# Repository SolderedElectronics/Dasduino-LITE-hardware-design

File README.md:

# Dasduino LITE Hardware Design

## About the Product

|  |
| :----------------------------------------------------------: |
| [Buy Dasduino LITE](https://www.solde.red/333008) |

Dasduino Lite is the right choice when you are limited with space, but still looking for capable controller. Based on Attiny1604, with USB-C port, Li-ion charger and CH340 USB-UART converter, it has all must-haves on a small form-factor.

Only 38mm wide and 26mm high, Dasduino Lite contains 12 GPIO pins. Of these, 9 can be programmed as analog. It comes with a USB Type-C connection and is 100% compatible with the original Arduino IDE software using  custom Board Definition. In addition to its small dimensions, which are the main characteristic of this Dasduino, there is also a charger for a lithium battery, a full RGB LED and an qwiic connector that will allow easy connection of the Dasduino Lite board with other devices. This Dasduino is extremely handy when you need to make a project that needs to take up as little space as possible.

---

## Repository Contents

This repository contains all design files for Dasduino LITE, organized as follows:

- **`CAD` folder**: Contains KiCAD design files, including:
  - Schematics
  - PCB layout
  - Panel PCB layout
  - Source 3D files in Fusion360, if any
  - All files are sorted by version with a detailed change log.
- **`OUTPUTS` folder**: Includes all production-ready files, such as:
  - Bill of Materials (BOM) and interactive BOM (iBOM)
  - PDF versions of schematics
  - 3D `.step` file of the board
  - 3D-printable models
  - Gerber files for PCB manufacturing
  - Image of the pinout of the board
  - Product image
  - Compliance, legal and generic sales documents

Refer to the `Change Log` in the CAD folder for details about updates between versions.

---

## Learn More About the Product

Beyond the repository, explore the following resources:

### Soldered Verify

The **Soldered Verify** system ensures every board you purchase from Soldered is fully functional. It also provides access to exclusive test data for your product. To get started, find the unique Soldered Verify ID on your product's packaging and enter the ID on the [Soldered Verify page](https://soldered.com/verify/) to access test results and additional product details.

### Soldered Community

Soldered Community is your go-to place for technical support. Our engineers track and answer all questions posted there, and it’s a great space for the maker community. Get answers to your questions and solutions for your challenges at [Soldered Community](https://soldered.com/community).

### solde.red

solde.red is an ultimate URL shortener and information hub. Access it by typing solde.red/ followed by your product SKU, e.g., [solde.red/333000](https://solde.red/333000), to find getting-started guides, datasheets, open-source hardware and software files, certifications, images, pinouts, and more. Read more about the shortener [here](https://solde.red/info/).

---

## Contributing

Contributions are welcome! Here’s how you can get involved:

- Submit pull requests to enhance the design or fix issues.
- Report bugs or problems by opening an issue.

We encourage community collaboration to make this product even better.

---

## About Soldered

[Soldered for Makers](https://soldered.com) specializes in designing and manufacturing electronic products tailored for enthusiasts, ranging from hobbyists to professionals. Our portfolio includes electronic boards, sensors, and actuators that are widely utilized in fields such as microelectronics, mechatronics, robotics, programming, and IoT. Every product we offer is designed in-house and built upon open-source hardware and software platforms. Proudly certified and manufactured within the European Union, our catalog likely includes the product you need for your project.

We complement these products with comprehensive tutorials and manuals, product descriptions, schematics, programming codes, and project examples. Our round-the-clock [customer and technical support](https://soldered.com/community) is available for all our products, irrespective of the sales channel. Soldered’s success and services reflect our maker community’s unwavering [trust](https://www.trustpilot.com/review/soldered.com), for which we are deeply grateful. Join our community and create using Soldered products.

---

## License

All Soldered open-source hardware (OSH) is under The TAPR Open Hardware License. Read more in the LICENSE file located in this repository.

**Disclaimer:**

No warranty - all designs in this repository are distributed in the hope that they will be useful, but without any warranty. They are provided "AS IS", therefore without warranty of any kind, either expressed or implied. The entire quality and performance of what you do with the contents of this repository are your responsibility. In no event Soldered Electronics will be liable for your damages, or losses, including any general, special, incidental, or consequential damage arising out of the use or inability to use the contents of this repository. 

---

## Have fun!

Thank you for your support from your fellow makers at Soldered Electronics.

Happy Making!

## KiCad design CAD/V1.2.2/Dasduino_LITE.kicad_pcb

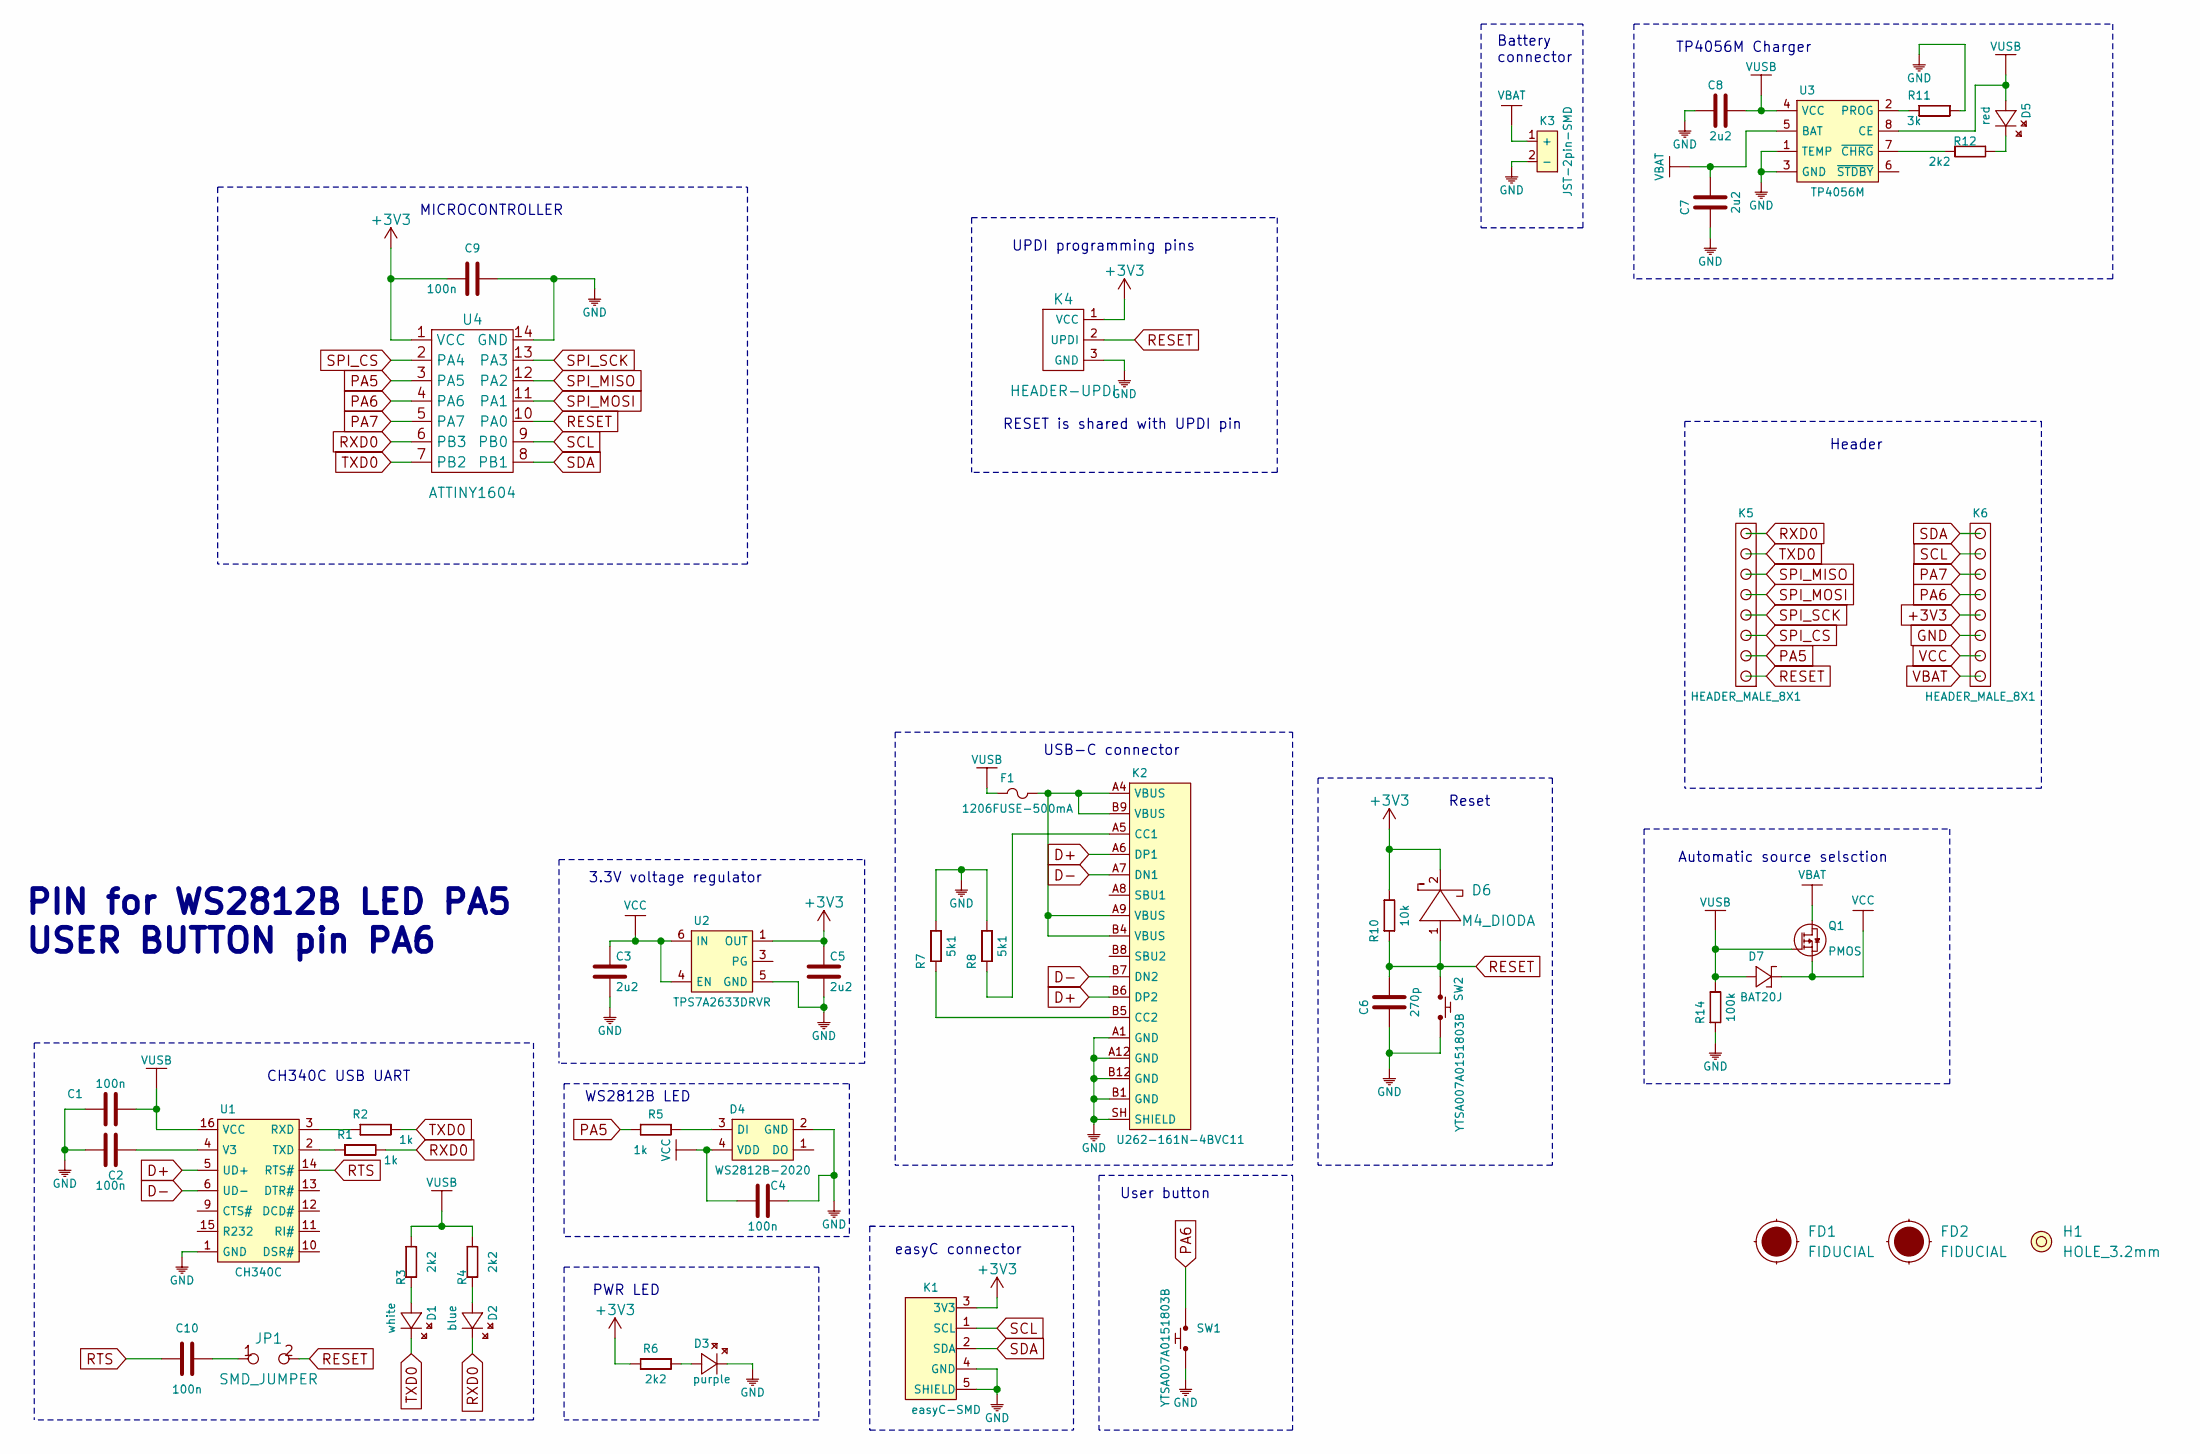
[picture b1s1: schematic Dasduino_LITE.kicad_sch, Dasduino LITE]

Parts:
C1, C2, C4, C9, C10: 100n; 0603C
C3, C5, C7, C8: 2u2; 0603C
C6: 270p; 0603C
D1: white; 0402LED
D2: blue; 0402LED
D3: purple; 0402LED
D4: WS2812B-2020
D5: red; 0402LED
D6: M4_DIODA
D7: BAT20J; SOD-323
F1: 1206FUSE-500mA; 1206FUSE
FD1, FD2: FIDUCIAL; FIDUCIAL_23
H1: HOLE_3.2mm
JP1: SMD_JUMPER
K1: easyC-SMD; easyC-connector
K2: U262-161N-4BVC11
K3: JST-2pin-SMD
K4: HEADER-UPDI
K5, K6: HEADER_MALE_8X1
Q1: PMOS; SOT-23-3
R1, R2, R5: 1k; 0603R
R3, R4, R6, R12: 2k2; 0402R
R7, R8: 5k1; 0603R
R10: 10k; 0603R
R11: 3k; 0603R
R14: 100k; 0603R
SW1, SW2: YTSA007A0151803B
U1: CH340C; SOP-16
U2: TPS7A2633DRVR
U3: TP4056M; TP4056M-MSOP8
U4: ATTINY1604; SOIC-14

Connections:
+3V3: C5.2, C9.1, D6.2 (K), K1.3 (3V3), K4.1 (VCC), K6.4, R6.1, R10.2, U2.1 (OUT), U4.1 (VCC)
D+: K2.A6 (DP1), K2.B6 (DP2), U1.5 (UD+)
D-: K2.A7 (DN1), K2.B7 (DN2), U1.6 (UD-)
GND: C1.1, C2.2, C3.1, C4.2, C5.1, C6.1, C7.1, C8.1, C9.2, D3.2 (K), D4.2 (GND), K1.4 (GND), K1.5 (SHIELD), K2.A1 (GND), K2.A12 (GND), K2.B1 (GND), K2.B12 (GND), K2.SH (SHIELD), K3.2 (-), K4.3 (GND), K6.3, R7.2, R8.2, R11.2, R14.1, SW1.1, SW2.2, U1.1 (GND), U2.5 (GND), U3.1 (TEMP), U3.3 (GND), U4.14 (GND)
unnamed: C2.1, U1.4 (V3)
unnamed: C10.2, JP1.1
unnamed: D1.1 (A), R3.1
unnamed: D2.1 (A), R4.1
unnamed: D3.1 (A), R6.2
unnamed: D4.3 (DI), R5.2
unnamed: D5.2 (K), R12.2
unnamed: F1.2, K2.A4 (VBUS), K2.A9 (VBUS), K2.B4 (VBUS), K2.B9 (VBUS)
unnamed: K2.A5 (CC1), R8.1
unnamed: K2.B5 (CC2), R7.1
unnamed: R1.1, U1.2 (TXD)
unnamed: R2.1, U1.3 (RXD)
unnamed: R11.1, U3.2 (PROG)
unnamed: R12.1, U3.7 (~CHRG)
PA5: K5.2, R5.1, U4.3 (PA5)
PA6: K6.5, SW1.2, U4.4 (PA6)
PA7: K6.6, U4.5 (PA7)
RESET: C6.2, D6.1 (A), JP1.2, K4.2 (UPDI), K5.1, R10.1, SW2.1, U4.10 (PA0)
RTS: C10.1, U1.14 (RTS#)
RXD0: D2.2 (K), K5.8, R1.2, U4.6 (PB3)
SCL: K1.1 (SCL), K6.7, U4.9 (PB0)
SDA: K1.2 (SDA), K6.8, U4.8 (PB1)
SPI_CS: K5.3, U4.2 (PA4)
SPI_MISO: K5.6, U4.12 (PA2)
SPI_MOSI: K5.5, U4.11 (PA1)
SPI_SCK: K5.4, U4.13 (PA3)
TXD0: D1.2 (K), K5.7, R2.2, U4.7 (PB2)
VBAT: C7.2, K3.1 (+), K6.1, Q1.3 (D), U3.5 (BAT)
VCC: C3.2, C4.1, D4.4 (VDD), D7.2 (K), K6.2, Q1.2 (S), U2.4 (EN), U2.6 (IN)
VUSB: C1.2, C8.2, D5.1 (A), D7.1 (A), F1.1, Q1.1 (G), R3.2, R4.2, R14.2, U1.16 (VCC), U3.4 (VCC), U3.8 (CE)

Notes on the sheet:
TP4056M Charger
PWR LED
UPDI programming pins
Header
3.3V voltage regulator
easyC connector
RESET is shared with UPDI pin
CH340C USB UART
User button
PIN for WS2812B LED PA5 USER BUTTON pin PA6
USB-C connector
WS2812B LED
MICROCONTROLLER
Battery connector
Reset
Automatic source selsction

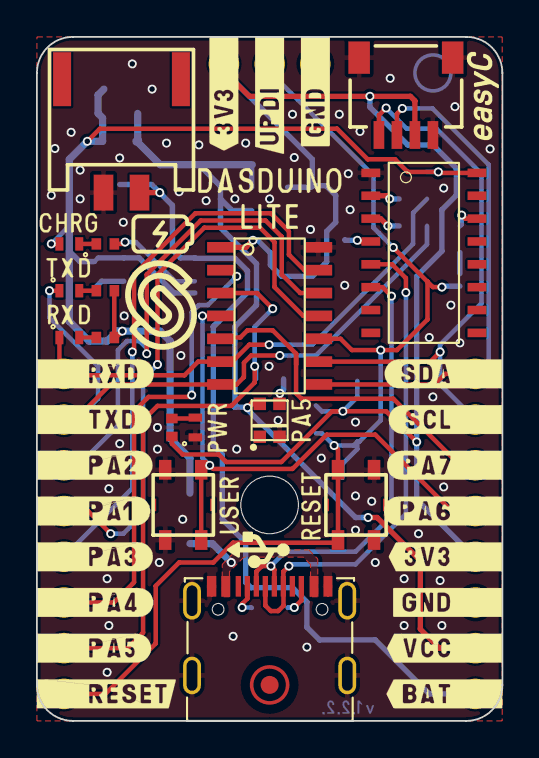
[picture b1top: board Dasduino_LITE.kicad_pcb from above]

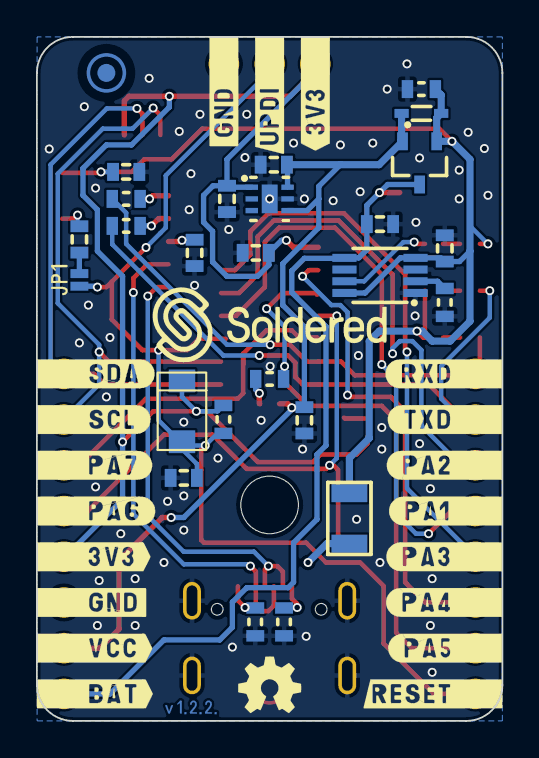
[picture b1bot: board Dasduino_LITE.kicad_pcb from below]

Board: 2 copper layers, 25.9 x 38.0 mm, 47 parts (28 on the bottom side), 34 nets.

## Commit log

2022-08-06 Updating open source files.
